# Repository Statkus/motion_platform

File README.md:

# Motion platform

Motion platform for simracing and flight simulation

## Servo motor driver parameters

Pn001: 4
Pn002: 2
Pn003: 0
Pn008: 300
Pn009: -300
Pn024: 10
Pn051: 3000
Pn052: 1 or -1 depending of how emergency stop is wired
Pn060: 2
Pn061: 6
Pn098: 10
Pn109: 1
Pn110: 30
Pn113: 20
Pn114: 10
Pn115: 100

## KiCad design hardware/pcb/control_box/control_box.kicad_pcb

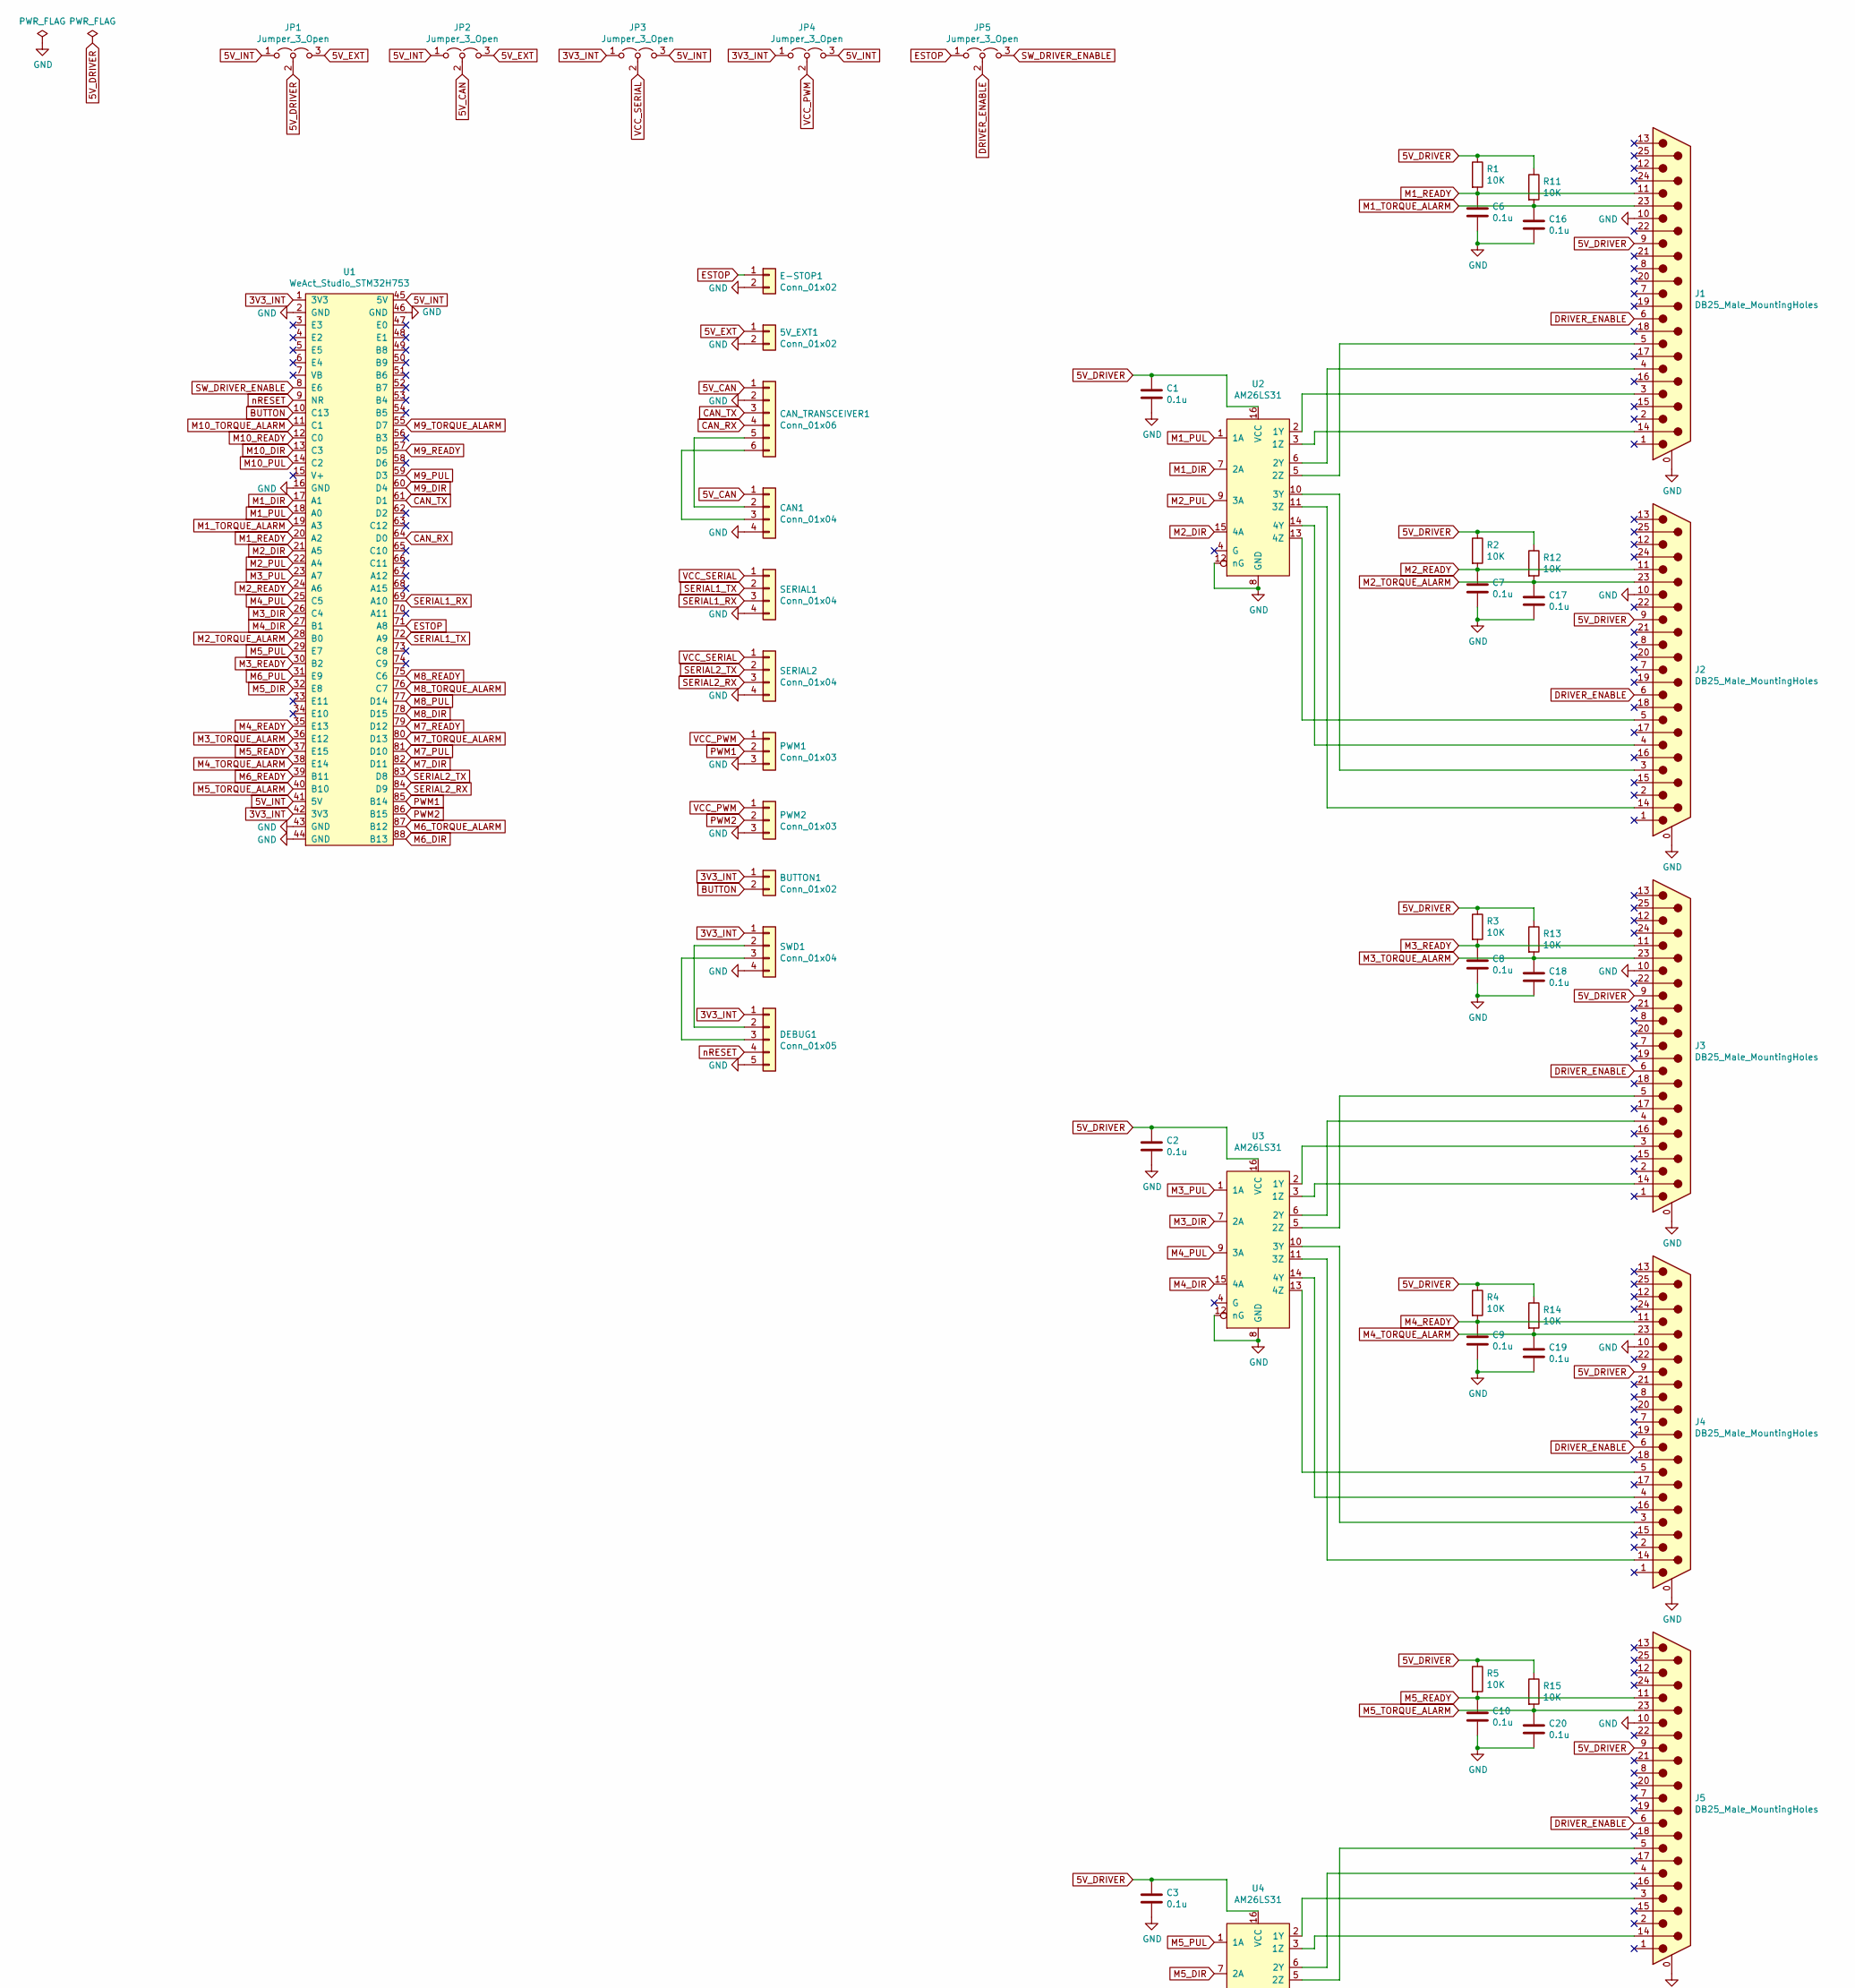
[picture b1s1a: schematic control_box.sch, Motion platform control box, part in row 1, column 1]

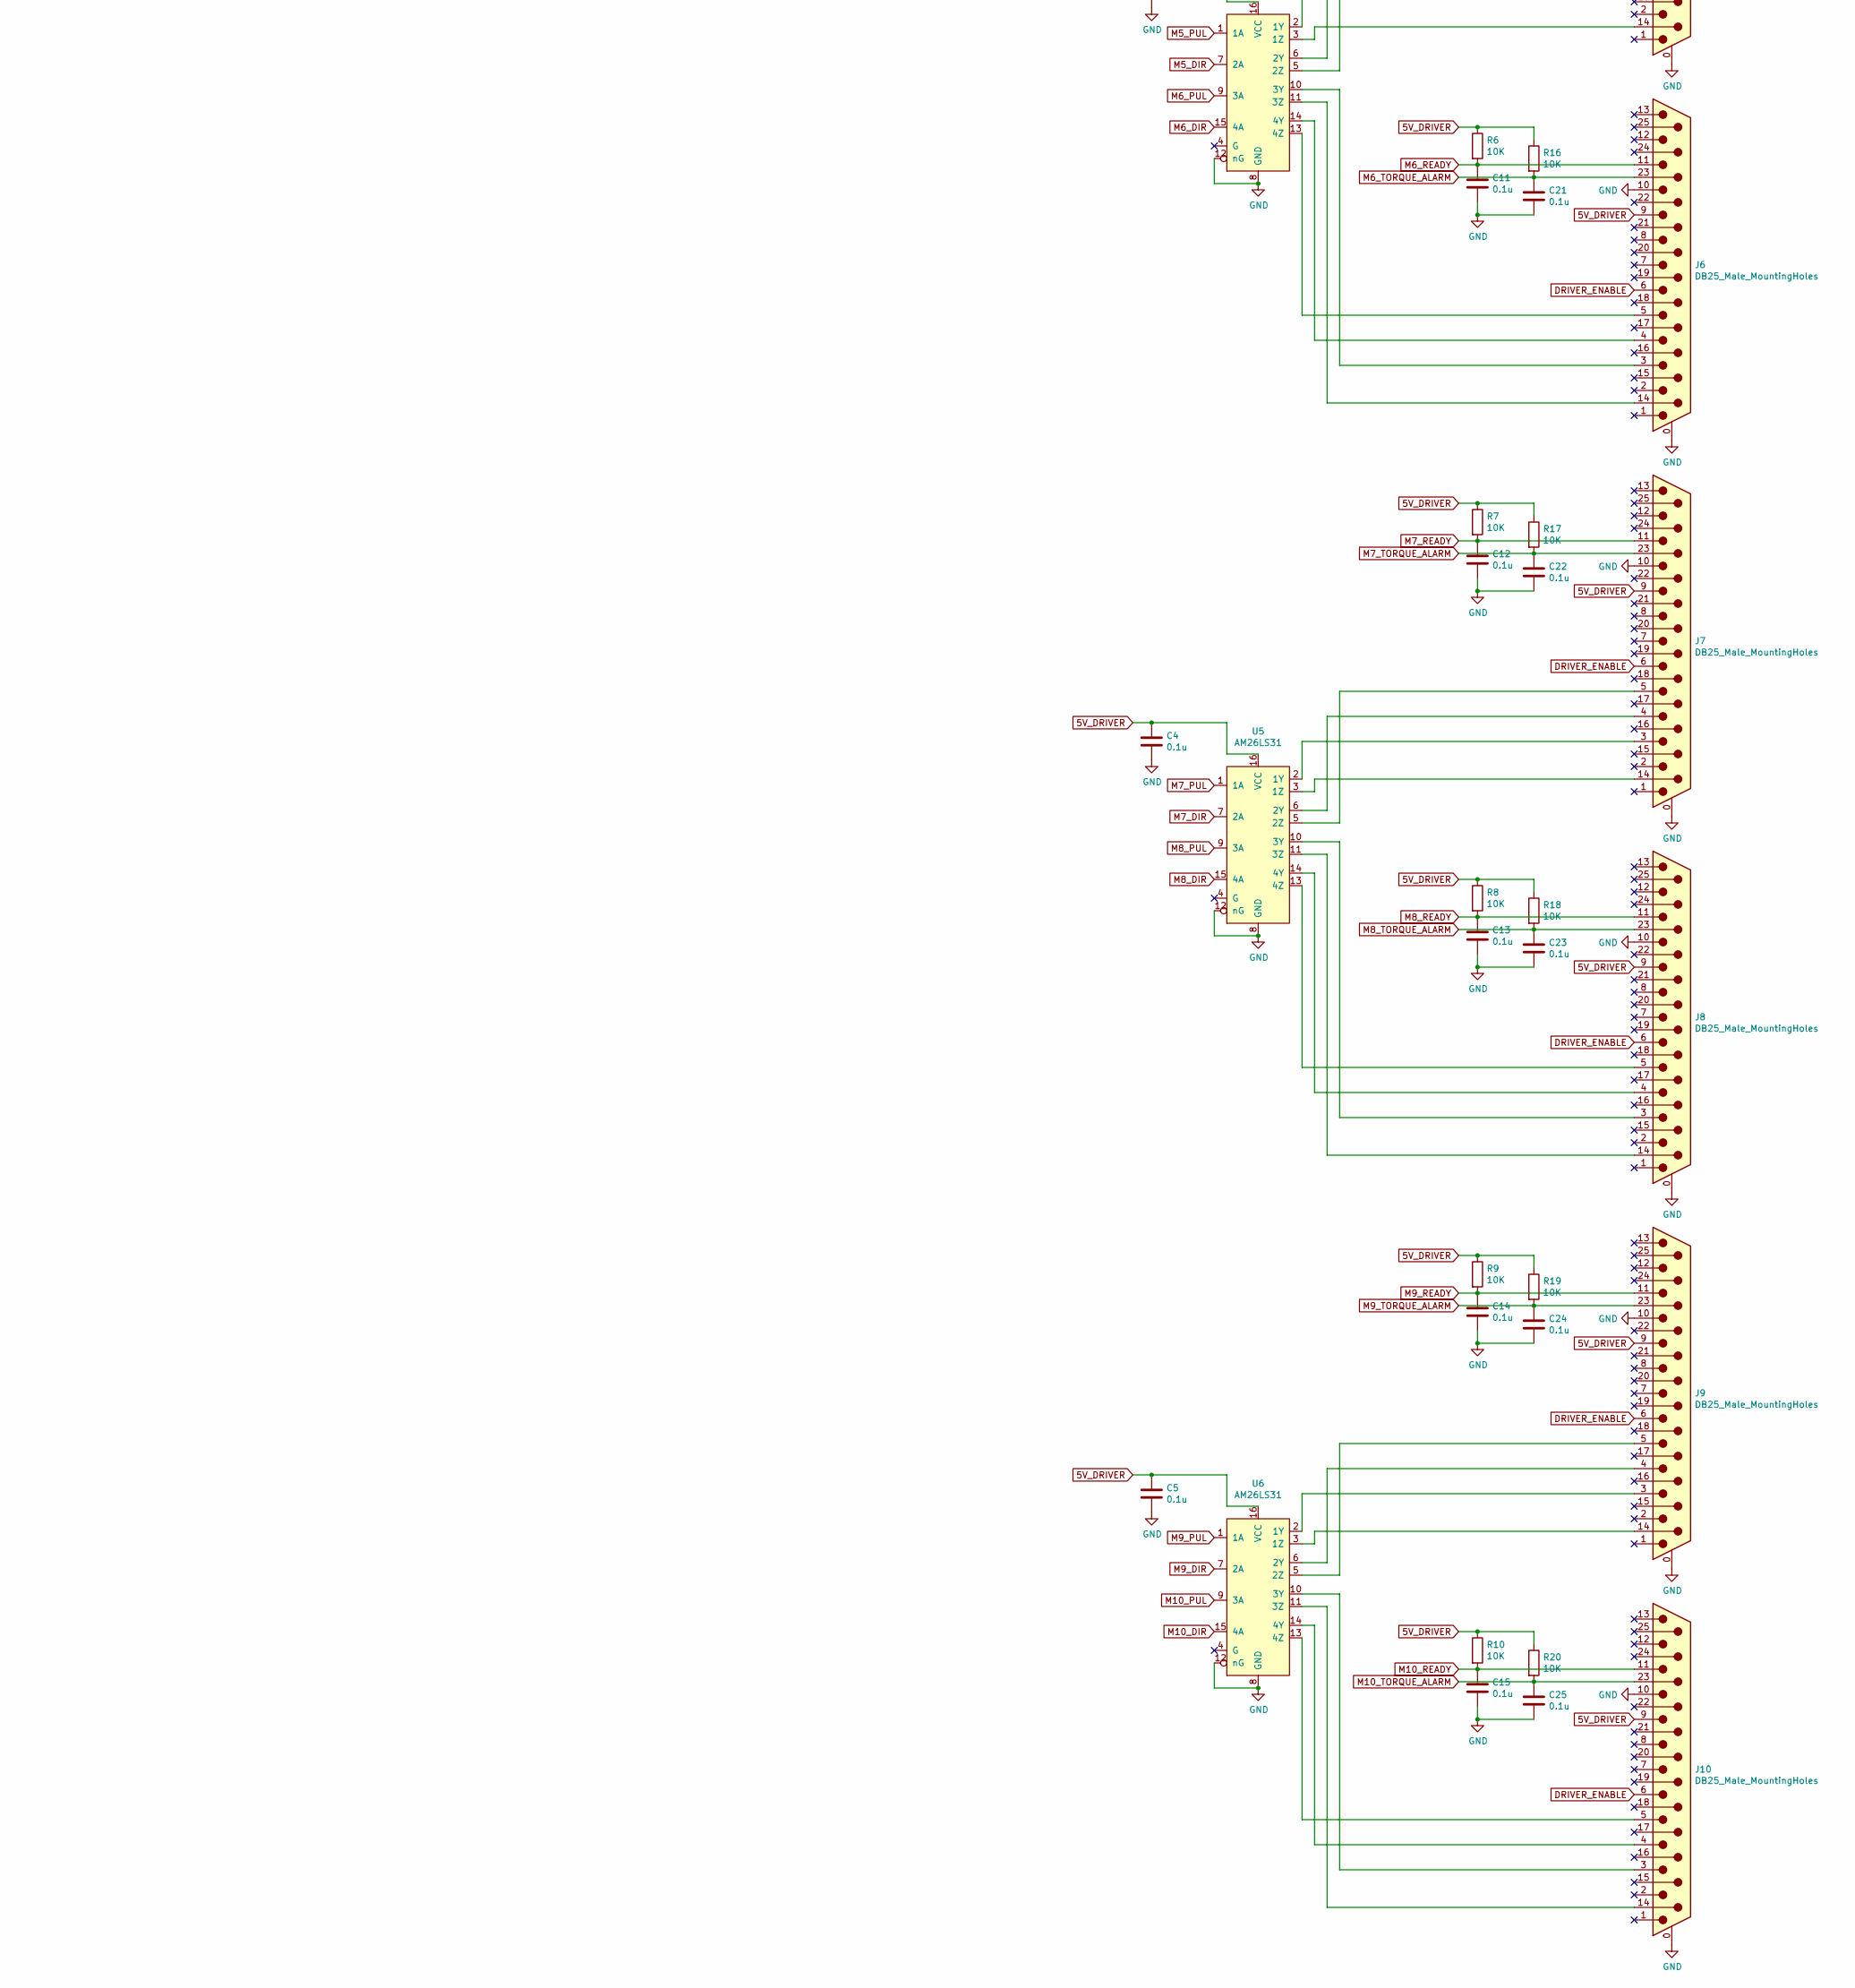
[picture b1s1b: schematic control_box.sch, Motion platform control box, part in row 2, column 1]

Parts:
5V_EXT1: Conn_01x02; PhoenixContact_MSTBA_2,5_2-G-5,08_1x02_P5.08mm_Horizontal
BUTTON1: Conn_01x02; PinHeader_1x02_P2.54mm_Vertical
C1, C2, C3, C4, C5, C6, C7, C8, C9, C10, C11, C12, C13, C14, C15, C16, C17, C18, C19, C20, C21, C22, C23, C24, C25: 0.1u; C_Disc_D4.3mm_W1.9mm_P5.00mm
CAN1: Conn_01x04; PhoenixContact_MSTBA_2,5_4-G-5,08_1x04_P5.08mm_Horizontal
CAN_TRANSCEIVER1: Conn_01x06; PinHeader_1x06_P2.54mm_Vertical
DEBUG1: Conn_01x05; PinHeader_1x05_P2.54mm_Horizontal
E-STOP1: Conn_01x02; PhoenixContact_MSTBA_2,5_2-G-5,08_1x02_P5.08mm_Horizontal
J1, J2, J3, J4, J5, J6, J7, J8, J9, J10: DB25_Male_MountingHoles; DSUB-25_Female_Vertical_P2.77x2.84mm_MountingHoles
JP1, JP2, JP3, JP4, JP5: Jumper_3_Open; PinHeader_1x03_P2.54mm_Vertical
PWM1, PWM2: Conn_01x03; PhoenixContact_MSTBA_2,5_3-G-5,08_1x03_P5.08mm_Horizontal
R1, R2, R3, R4, R5, R6, R7, R8, R9, R10, R11, R12, R13, R14, R15, R16, R17, R18, R19, R20: 10K; R_Axial_DIN0204_L3.6mm_D1.6mm_P2.54mm_Vertical
SERIAL1: Conn_01x04; PinHeader_1x04_P2.54mm_Vertical
SERIAL2: Conn_01x04; PhoenixContact_MSTBA_2,5_4-G-5,08_1x04_P5.08mm_Horizontal
SWD1: Conn_01x04; PinHeader_1x04_P2.54mm_Vertical
U1: WeAct_Studio_STM32H753; WeAct_Studio_STM32H743
U2, U3, U4, U5, U6: AM26LS31; DIP-16_W7.62mm

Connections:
3V3_INT: BUTTON1.1, DEBUG1.1, JP3.1 (A), JP4.1 (A), SWD1.1, U1.1 (3V3), U1.42 (3V3)
5V_CAN: CAN1.1, CAN_TRANSCEIVER1.1, JP2.2 (C)
5V_DRIVER: C1.1, C2.1, C3.1, C4.1, C5.1, J1.9, J2.9, J3.9, J4.9, J5.9, J6.9, J7.9, J8.9, J9.9, J10.9, JP1.2 (C), R1.1, R2.1, R3.1, R4.1, R5.1, R6.1, R7.1, R8.1, R9.1, R10.1, R11.1, R12.1, R13.1, R14.1, R15.1, R16.1, R17.1, R18.1, R19.1, R20.1, U2.16 (VCC), U3.16 (VCC), U4.16 (VCC), U5.16 (VCC), U6.16 (VCC)
5V_EXT: 5V_EXT1.1, JP1.3 (B), JP2.3 (B)
5V_INT: JP1.1 (A), JP2.1 (A), JP3.3 (B), JP4.3 (B), U1.41 (5V), U1.45 (5V)
BUTTON: BUTTON1.2, U1.10 (C13)
CAN_RX: CAN_TRANSCEIVER1.4, U1.64 (D0)
CAN_TX: CAN_TRANSCEIVER1.3, U1.61 (D1)
DRIVER_ENABLE: J1.6, J2.6, J3.6, J4.6, J5.6, J6.6, J7.6, J8.6, J9.6, J10.6, JP5.2 (C)
ESTOP: E-STOP1.1, JP5.1 (A), U1.71 (A8)
GND: 5V_EXT1.2, C1.2, C2.2, C3.2, C4.2, C5.2, C6.2, C7.2, C8.2, C9.2, C10.2, C11.2, C12.2, C13.2, C14.2, C15.2, C16.2, C17.2, C18.2, C19.2, C20.2, C21.2, C22.2, C23.2, C24.2, C25.2, CAN1.4, CAN_TRANSCEIVER1.2, DEBUG1.5, E-STOP1.2, J1.0 (PAD), J1.10, J2.0 (PAD), J2.10, J3.0 (PAD), J3.10, J4.0 (PAD), J4.10, J5.0 (PAD), J5.10, J6.0 (PAD), J6.10, J7.0 (PAD), J7.10, J8.0 (PAD), J8.10, J9.0 (PAD), J9.10, J10.0 (PAD), J10.10, PWM1.3, PWM2.3, SERIAL1.4, SERIAL2.4, SWD1.4, U1.2 (GND), U1.16 (GND), U1.43 (GND), U1.44 (GND), U1.46 (GND), U2.8 (GND), U2.12 (nG), U3.8 (GND), U3.12 (nG), U4.8 (GND), U4.12 (nG), U5.8 (GND), U5.12 (nG), U6.8 (GND), U6.12 (nG)
M1_DIR: U1.17 (A1), U2.7 (2A)
M1_PUL: U1.18 (A0), U2.1 (1A)
M1_READY: C6.1, J1.11, R1.2, U1.20 (A2)
M1_TORQUE_ALARM: C16.1, J1.23, R11.2, U1.19 (A3)
M2_DIR: U1.21 (A5), U2.15 (4A)
M2_PUL: U1.22 (A4), U2.9 (3A)
M2_READY: C7.1, J2.11, R2.2, U1.24 (A6)
M2_TORQUE_ALARM: C17.1, J2.23, R12.2, U1.28 (B0)
M3_DIR: U1.26 (C4), U3.7 (2A)
M3_PUL: U1.23 (A7), U3.1 (1A)
M3_READY: C8.1, J3.11, R3.2, U1.30 (B2)
M3_TORQUE_ALARM: C18.1, J3.23, R13.2, U1.36 (E12)
M4_DIR: U1.27 (B1), U3.15 (4A)
M4_PUL: U1.25 (C5), U3.9 (3A)
M4_READY: C9.1, J4.11, R4.2, U1.35 (E13)
M4_TORQUE_ALARM: C19.1, J4.23, R14.2, U1.38 (E14)
M5_DIR: U1.32 (E8), U4.7 (2A)
M5_PUL: U1.29 (E7), U4.1 (1A)
M5_READY: C10.1, J5.11, R5.2, U1.37 (E15)
M5_TORQUE_ALARM: C20.1, J5.23, R15.2, U1.40 (B10)
M6_DIR: U1.88 (B13), U4.15 (4A)
M6_PUL: U1.31 (E9), U4.9 (3A)
M6_READY: C11.1, J6.11, R6.2, U1.39 (B11)
M6_TORQUE_ALARM: C21.1, J6.23, R16.2, U1.87 (B12)
M7_DIR: U1.82 (D11), U5.7 (2A)
M7_PUL: U1.81 (D10), U5.1 (1A)
M7_READY: C12.1, J7.11, R7.2, U1.79 (D12)
M7_TORQUE_ALARM: C22.1, J7.23, R17.2, U1.80 (D13)
M8_DIR: U1.78 (D15), U5.15 (4A)
M8_PUL: U1.77 (D14), U5.9 (3A)
M8_READY: C13.1, J8.11, R8.2, U1.75 (C6)
M8_TORQUE_ALARM: C23.1, J8.23, R18.2, U1.76 (C7)
M9_DIR: U1.60 (D4), U6.7 (2A)
M9_PUL: U1.59 (D3), U6.1 (1A)
M9_READY: C14.1, J9.11, R9.2, U1.57 (D5)
M9_TORQUE_ALARM: C24.1, J9.23, R19.2, U1.55 (D7)
M10_DIR: U1.13 (C3), U6.15 (4A)
M10_PUL: U1.14 (C2), U6.9 (3A)
M10_READY: C15.1, J10.11, R10.2, U1.12 (C0)
M10_TORQUE_ALARM: C25.1, J10.23, R20.2, U1.11 (C1)
unnamed: CAN1.2, CAN_TRANSCEIVER1.5
unnamed: CAN1.3, CAN_TRANSCEIVER1.6
unnamed: DEBUG1.2, SWD1.2
unnamed: DEBUG1.3, SWD1.3
unnamed: J1.3, U2.2 (1Y)
unnamed: J1.4, U2.6 (2Y)
unnamed: J1.5, U2.5 (2Z)
unnamed: J1.14, U2.3 (1Z)
unnamed: J2.3, U2.10 (3Y)
unnamed: J2.4, U2.14 (4Y)
unnamed: J2.5, U2.13 (4Z)
unnamed: J2.14, U2.11 (3Z)
unnamed: J3.3, U3.2 (1Y)
unnamed: J3.4, U3.6 (2Y)
unnamed: J3.5, U3.5 (2Z)
unnamed: J3.14, U3.3 (1Z)
unnamed: J4.3, U3.10 (3Y)
unnamed: J4.4, U3.14 (4Y)
unnamed: J4.5, U3.13 (4Z)
unnamed: J4.14, U3.11 (3Z)
unnamed: J5.3, U4.2 (1Y)
unnamed: J5.4, U4.6 (2Y)
unnamed: J5.5, U4.5 (2Z)
unnamed: J5.14, U4.3 (1Z)
unnamed: J6.3, U4.10 (3Y)
unnamed: J6.4, U4.14 (4Y)
unnamed: J6.5, U4.13 (4Z)
unnamed: J6.14, U4.11 (3Z)
unnamed: J7.3, U5.2 (1Y)
unnamed: J7.4, U5.6 (2Y)
unnamed: J7.5, U5.5 (2Z)
unnamed: J7.14, U5.3 (1Z)
unnamed: J8.3, U5.10 (3Y)
unnamed: J8.4, U5.14 (4Y)
unnamed: J8.5, U5.13 (4Z)
unnamed: J8.14, U5.11 (3Z)
unnamed: J9.3, U6.2 (1Y)
unnamed: J9.4, U6.6 (2Y)
unnamed: J9.5, U6.5 (2Z)
unnamed: J9.14, U6.3 (1Z)
unnamed: J10.3, U6.10 (3Y)
unnamed: J10.4, U6.14 (4Y)
unnamed: J10.5, U6.13 (4Z)
unnamed: J10.14, U6.11 (3Z)
PWM1: PWM1.2, U1.85 (B14)
PWM2: PWM2.2, U1.86 (B15)
SERIAL1_RX: SERIAL1.3, U1.69 (A10)
SERIAL1_TX: SERIAL1.2, U1.72 (A9)
SERIAL2_RX: SERIAL2.3, U1.84 (D9)
SERIAL2_TX: SERIAL2.2, U1.83 (D8)
SW_DRIVER_ENABLE: JP5.3 (B), U1.8 (E6)
VCC_PWM: JP4.2 (C), PWM1.1, PWM2.1
VCC_SERIAL: JP3.2 (C), SERIAL1.1, SERIAL2.1
nRESET: DEBUG1.4, U1.9 (NR)

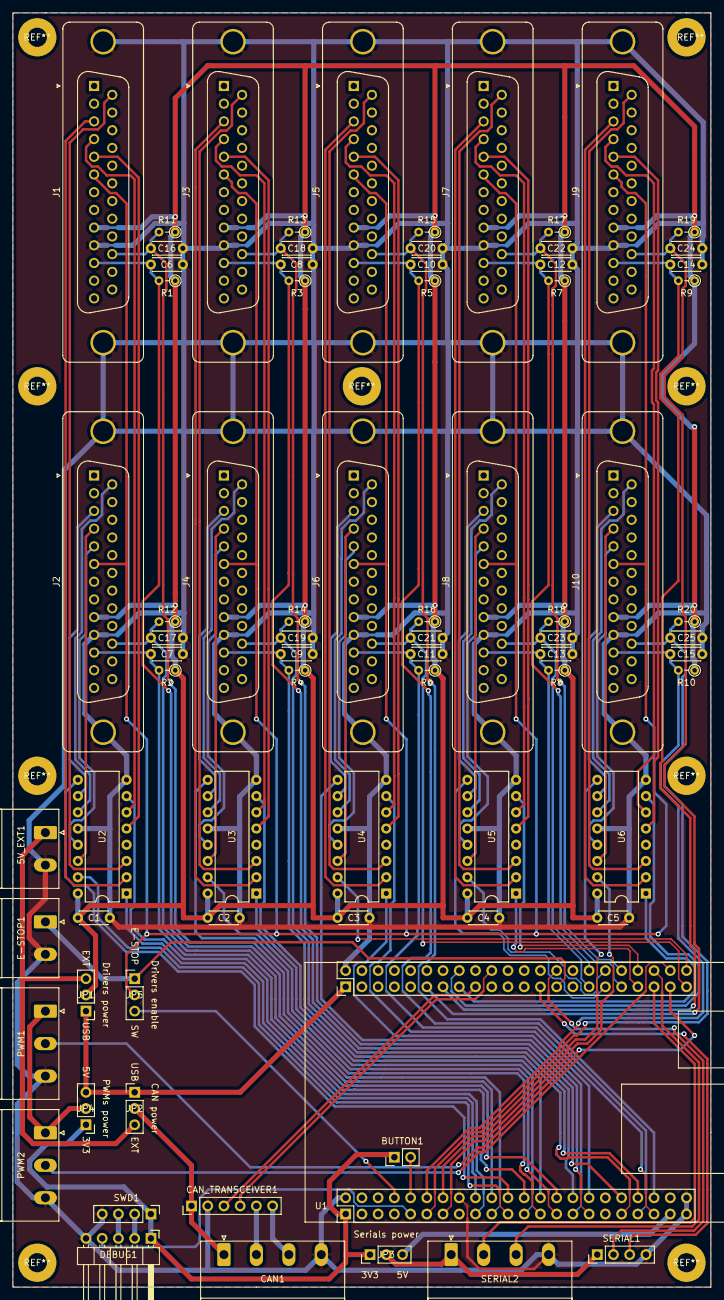
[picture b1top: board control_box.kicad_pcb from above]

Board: 2 copper layers, 109.2 x 199.4 mm, 77 parts (0 on the bottom side), 105 nets.

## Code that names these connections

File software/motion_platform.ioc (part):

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Mcu.Name=STM32H743VITx
Mcu.Package=LQFP100
Mcu.UserName=STM32H743VITx
PA0.GPIOParameters=GPIO_Speed,GPIO_Label
PA0.GPIO_Label=M1_PUL
PA0.GPIO_Speed=GPIO_SPEED_FREQ_VERY_HIGH
PA0.Signal=GPIO_Output
PA1.GPIOParameters=GPIO_Speed,GPIO_Label
PA1.GPIO_Label=M1_DIR
PA1.GPIO_Speed=GPIO_SPEED_FREQ_VERY_HIGH
PA1.Signal=GPIO_Output
PA10.GPIOParameters=GPIO_Label
PA10.GPIO_Label=SERIAL1_RX
PA10.Mode=Asynchronous
PA10.Signal=USART1_RX
PA11.Mode=Device_Only
PA11.Signal=USB_OTG_FS_DM
PA12.Mode=Device_Only
PA12.Signal=USB_OTG_FS_DP
PA15\ (JTDI).Signal=SPI1_NSS
PA2.GPIOParameters=GPIO_Label
PA2.GPIO_Label=M1_READY
PA2.Signal=GPIO_Input
PA3.GPIOParameters=GPIO_Label
PA3.GPIO_Label=M1_TORQUE_ALARM
PA3.Signal=GPIO_Input
PA4.GPIOParameters=GPIO_Speed,GPIO_Label
PA4.GPIO_Label=M2_PUL
PA4.GPIO_Speed=GPIO_SPEED_FREQ_VERY_HIGH
PA4.Signal=GPIO_Output
PA5.GPIOParameters=GPIO_Speed,GPIO_Label
PA5.GPIO_Label=M2_DIR
PA5.GPIO_Speed=GPIO_SPEED_FREQ_VERY_HIGH
PA5.Signal=GPIO_Output
PA6.GPIOParameters=GPIO_Label
PA6.GPIO_Label=M2_READY
PA6.Signal=GPIO_Input
PA7.GPIOParameters=GPIO_Speed,GPIO_Label
PA7.GPIO_Label=M3_PUL
PA7.GPIO_Speed=GPIO_SPEED_FREQ_VERY_HIGH
PA7.Signal=GPIO_Output
PA8.GPIOParameters=GPIO_Label
PA8.GPIO_Label=ESTOP
PA8.Signal=GPIO_Input
PA9.GPIOParameters=GPIO_Label
PA9.GPIO_Label=SERIAL1_TX
PA9.Mode=Asynchronous
PA9.Signal=USART1_TX
PB0.GPIOParameters=GPIO_Label
PB0.GPIO_Label=M2_TORQUE_ALARM
PB0.Signal=GPIO_Input
PB1.GPIOParameters=GPIO_Speed,GPIO_Label
PB1.GPIO_Label=M4_DIR
PB1.GPIO_Speed=GPIO_SPEED_FREQ_VERY_HIGH
PB1.Signal=GPIO_Output
PB10.GPIOParameters=GPIO_Label
PB10.GPIO_Label=M5_TORQUE_ALARM
PB10.Signal=GPIO_Input
PB11.GPIOParameters=GPIO_Label
PB11.GPIO_Label=M6_READY
PB11.Signal=GPIO_Input
PB12.GPIOParameters=GPIO_Label
PB12.GPIO_Label=M6_TORQUE_ALARM
PB12.Signal=GPIO_Input
PB13.GPIOParameters=GPIO_Speed,GPIO_Label
PB13.GPIO_Label=M6_DIR
PB13.GPIO_Speed=GPIO_SPEED_FREQ_VERY_HIGH
PB13.Signal=GPIO_Output
PB14.GPIOParameters=GPIO_Label
PB14.GPIO_Label=PWM1
PB14.Signal=S_TIM12_CH1
PB15.GPIOParameters=GPIO_Label
PB15.GPIO_Label=PWM2
PB15.Signal=S_TIM12_CH2
PB2.GPIOParameters=GPIO_Label
PB2.GPIO_Label=M3_READY
PB2.Signal=GPIO_Input
PB4\ (NJTRST).Signal=SPI1_MISO
PB6.Signal=QUADSPI_BK1_NCS
PB8.Signal=I2C1_SCL
PB9.Signal=I2C1_SDA
PC0.GPIOParameters=GPIO_Label
PC0.GPIO_Label=M10_READY
PC0.Signal=GPIO_Input
PC1.GPIOParameters=GPIO_Label
PC1.GPIO_Label=M10_TORQUE_ALARM
PC1.Signal=GPIO_Input
PC10.Mode=SD_4_bits_Wide_bus
PC10.Signal=SDMMC1_D2
PC11.Mode=SD_4_bits_Wide_bus
PC11.Signal=SDMMC1_D3
PC12.Mode=SD_4_bits_Wide_bus
PC12.Signal=SDMMC1_CK
PC13.GPIOParameters=GPIO_PuPd,GPIO_Label
PC13.GPIO_Label=BUTTON
PC13.GPIO_PuPd=GPIO_PULLDOWN
PC13.Signal=GPIO_Input
PC2_C.GPIOParameters=GPIO_Label
PC2_C.GPIO_Label=M10_PUL
PC2_C.Signal=GPIO_Output
PC3_C.GPIOParameters=GPIO_Label
PC3_C.GPIO_Label=M10_DIR
PC3_C.Signal=GPIO_Output
PC4.GPIOParameters=GPIO_Speed,GPIO_Label
PC4.GPIO_Label=M3_DIR
PC4.GPIO_Speed=GPIO_SPEED_FREQ_VERY_HIGH
PC4.Signal=GPIO_Output
PC5.GPIOParameters=GPIO_Speed,GPIO_Label
PC5.GPIO_Label=M4_PUL
PC5.GPIO_Speed=GPIO_SPEED_FREQ_VERY_HIGH
PC5.Signal=GPIO_Output
PC6.GPIOParameters=GPIO_Label
PC6.GPIO_Label=M8_READY
PC6.Signal=GPIO_Input
PC7.GPIOParameters=GPIO_Label
PC7.GPIO_Label=M8_TORQUE_ALARM
PC7.Signal=GPIO_Input
PC8.Mode=SD_4_bits_Wide_bus
PC8.Signal=SDMMC1_D0
PC9.Mode=SD_4_bits_Wide_bus
PC9.Signal=SDMMC1_D1
PD0.GPIOParameters=GPIO_Label
PD0.GPIO_Label=CAN_RX
PD0.Mode=FDCAN_Activate
PD0.Signal=FDCAN1_RX
PD1.GPIOParameters=GPIO_Label
PD1.GPIO_Label=CAN_TX
PD1.Mode=FDCAN_Activate
PD1.Signal=FDCAN1_TX
PD10.GPIOParameters=GPIO_Label
PD10.GPIO_Label=M7_PUL
PD10.Signal=GPIO_Output
PD11.GPIOParameters=GPIO_Label
PD11.GPIO_Label=M7_DIR
PD11.Signal=GPIO_Output
PD12.GPIOParameters=GPIO_Label
PD12.GPIO_Label=M7_READY
PD12.Signal=GPIO_Input
PD13.GPIOParameters=GPIO_Label
PD13.GPIO_Label=M7_TORQUE_ALARM
PD13.Signal=GPIO_Input
PD14.GPIOParameters=GPIO_Label
PD14.GPIO_Label=M8_PUL
PD14.Signal=GPIO_Output
PD15.GPIOParameters=GPIO_Label
PD15.GPIO_Label=M8_DIR
PD15.Signal=GPIO_Output
PD2.Mode=SD_4_bits_Wide_bus
PD2.Signal=SDMMC1_CMD
PD3.GPIOParameters=GPIO_Label
PD3.GPIO_Label=M9_PUL
PD3.Signal=GPIO_Output
PD4.GPIOParameters=GPIO_Label
PD4.GPIO_Label=M9_DIR
PD4.Signal=GPIO_Output
PD5.GPIOParameters=GPIO_Label
PD5.GPIO_Label=M9_READY
PD5.Signal=GPIO_Input
PD6.GPIOParameters=GPIO_Label
PD6.GPIO_Label=SPI_FLASH_CS
PD6.Signal=GPIO_Input
PD7.GPIOParameters=GPIO_Label
PD7.GPIO_Label=M9_TORQUE_ALARM
PD7.Signal=GPIO_Input
PD8.GPIOParameters=GPIO_Label
PD8.GPIO_Label=SERIAL2_TX
PD8.Mode=Asynchronous
PD8.Signal=USART3_TX
PD9.GPIOParameters=GPIO_Label
PD9.GPIO_Label=SERIAL2_RX
PD9.Mode=Asynchronous
PD9.Signal=USART3_RX
PE10.Signal=TIM1_CH2N
PE11.GPIOParameters=GPIO_Label
PE11.GPIO_Label=LCD_CS
PE11.Signal=GPIO_Input
PE12.GPIOParameters=GPIO_Label
PE12.GPIO_Label=M3_TORQUE_ALARM
PE12.Signal=GPIO_Input
PE13.GPIOParameters=GPIO_Label
PE13.GPIO_Label=M4_READY
PE13.Signal=GPIO_Input
PE14.GPIOParameters=GPIO_Label
PE14.GPIO_Label=M4_TORQUE_ALARM
PE14.Signal=GPIO_Input
PE15.GPIOParameters=GPIO_Label
PE15.GPIO_Label=M5_READY
PE15.Signal=GPIO_Input
PE3.GPIOParameters=GPIO_Speed,GPIO_Label
PE3.GPIO_Label=LED
PE3.GPIO_Speed=GPIO_SPEED_FREQ_HIGH
PE3.Signal=GPIO_Output
PE6.GPIOParameters=GPIO_Label
PE6.GPIO_Label=SW_DRIVER_ENABLE
PE6.Signal=GPIO_Output
PE7.GPIOParameters=GPIO_Speed,GPIO_Label
PE7.GPIO_Label=M5_PUL
PE7.GPIO_Speed=GPIO_SPEED_FREQ_VERY_HIGH
PE7.Signal=GPIO_Output
PE8.GPIOParameters=GPIO_Speed,GPIO_Label
PE8.GPIO_Label=M5_DIR
PE8.GPIO_Speed=GPIO_SPEED_FREQ_VERY_HIGH
PE8.Signal=GPIO_Output
PE9.GPIOParameters=GPIO_Speed,GPIO_Label
PE9.GPIO_Label=M6_PUL
PE9.GPIO_Speed=GPIO_SPEED_FREQ_VERY_HIGH
PE9.Signal=GPIO_Output
PH0-OSC_IN\ (PH0).Mode=HSE-External-Oscillator
PH0-OSC_IN\ (PH0).Signal=RCC_OSC_IN
PH1-OSC_OUT\ (PH1).Mode=HSE-External-Oscillator
PH1-OSC_OUT\ (PH1).Signal=RCC_OSC_OUT
RCC.SYSCLKFreq_VALUE=480000000
RCC.SYSCLKSource=RCC_SYSCLKSOURCE_PLLCLK
board=custom

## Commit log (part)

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2025-08-11 [GIT] Add gitignore file
2025-08-11 [3D] Add 3D parts library
2025-08-11 [3D] Add base platform
2025-08-11 [3D] Add seat mover surge platform
2025-08-11 [3D] Add seat mover sway platform
2025-08-11 [3D] Add seat mover seat platform
2025-08-11 [3D] Add seat mover assembly
2025-08-25 [3D] Add final assembly
2025-09-17 [GIT] Add git attributes to allow git diff on FreeCAD files
    Also run "git config diff.strings.textconv strings" for this to work
2025-09-17 [3D] Add exported STL files to print
2025-09-22 [GEN] Add generated code
2025-09-22 [BUILD] Add OpenOCD configuration file for STM32H743
2025-09-22 [GIT] Update gitignore file for software build files
2025-09-22 [DEV] Implement first version
2025-09-22 [PROFILE] Add FlyPT Mover profiles
2025-09-23 [GEN] Update generated code
2025-09-23 [DEV] Add homing behavior
2025-09-23 [DOC] Add servo motor driver parameters value to change
2025-10-09 [DEV] Improve motors calibration
2025-10-09 [3D] Add main breaker mount for electrical panel
2025-10-09 [3D] Add parts for 2020 profile
2025-10-09 [GEN] Update generated code
    Update STM32CubeMX and firmware version and add GPIO for 6 motors
2025-10-20 [3D] Add corner bracket for M5 on 2020 profile
2025-10-22 [DEV] Use integer type for motors position
2025-10-22 [DEV] Remove on the fly max speed and acceleration configuration
2025-11-24 [3D] Add corner bracket for M5/M3 on 2020 profile with long side
2025-11-24 [3D] Add zip tie mount for 4040 profile
2025-11-24 [BUILD] Print memory usage
2025-11-24 [DEV] Update to 6 motors
2025-11-28 [3D] Add foot for 3DOF base platform
2025-12-08 [PROFILE] Update flypt mover car profile for seat mover
2025-12-09 [DEV] Adjust motors max speed and acceleration
2025-12-10 [PROFILE] Update FlyPT Mover profile
2025-12-10 [GEN] Update generated code to change GPIOs for fan and shaker
2025-12-10 [DEV] Update timer used for fan and shaker
2025-12-10 [DOC] Update servo driver parameters value
2026-01-13 [3D] Add pulley to tension harness in surge axis
2026-01-13 [PCB] Add control box PCB KiCad design
2026-01-15 [3D] Add control box case
2026-01-15 [DEV] Reduce motors speed during calibration
2026-02-16 [PROFILE] Update FlyPT Mover car profile
2026-04-16 WIP new STM32CubeMX IOs
